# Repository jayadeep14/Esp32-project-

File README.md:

# Esp32 Project
## [ESP32 Bluetooth speaker ](https://github.com/jayadeep14/Esp32-project-/tree/Bt_speaker).
###      Custom ESP32 Bluetooth speaker
         Creating a custom bluetooth speaker using esp32.Esp32 for bluetooth connectivity , a DAC (Digital-to-Analog  
         Converter) for audio quality, potentially an amplifier, and a battery with a charging circuit.

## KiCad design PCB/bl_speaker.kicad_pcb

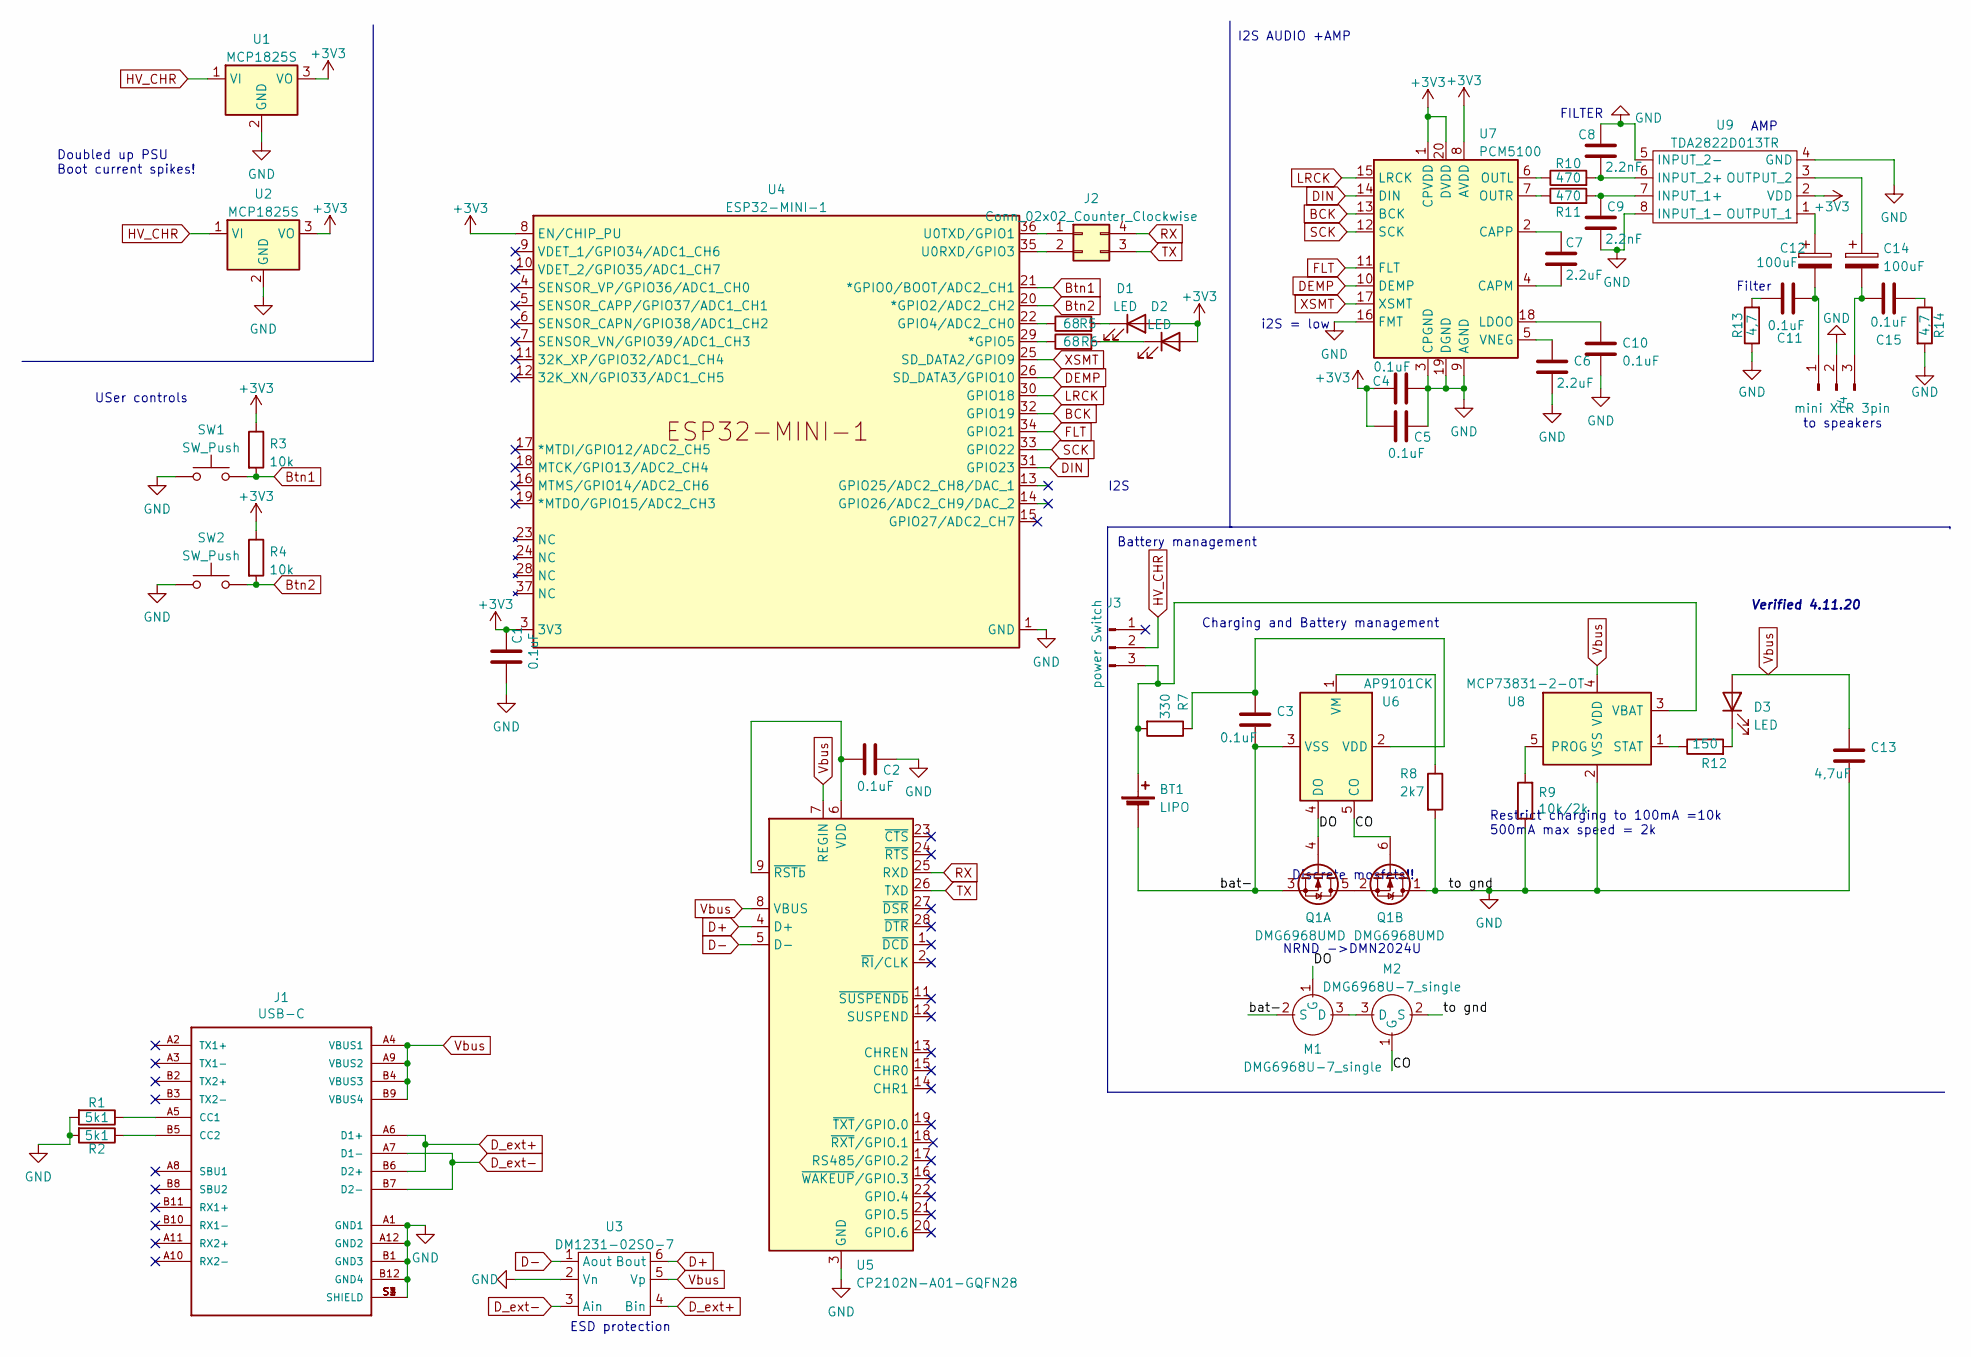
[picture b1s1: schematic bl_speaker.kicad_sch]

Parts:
BT1: LIPO; PinHeader_1x02_P2.54mm_Vertical
C1, C2, C3, C4, C5, C10, C11, C15: 0.1uF; C_0603_1608Metric
C6, C7: 2.2uF; C_0805_2012Metric
C8, C9: 2.2nF; C_0603_1608Metric
C12, C14: 100uF; CP_Elec_8x10
C13: 4,7uF; C_0603_1608Metric
D1, D2, D3: LED; LED_0603_1608Metric
J1: USB-C; MOLEX_105450-0101
J2: Conn_02x02_Counter_Clockwise; PinHeader_2x02_P2.54mm_Vertical
J3: power Switch; PinHeader_1x03_P2.54mm_Vertical
J4: mini XLR 3pin; PinHeader_1x03_P2.54mm_Vertical
M1, M2: DMG6968U-7_single; TSOT-23
Q1: DMG6968UMD; SOT-23-6_Handsoldering
R1, R2: 5k1; R_0603_1608Metric
R3, R4: 10k; R_0603_1608Metric
R5, R6: 68; R_0603_1608Metric
R7: 330; R_0603_1608Metric
R8: 2k7; R_0603_1608Metric
R9: 10k/2k; R_0603_1608Metric
R10, R11: 470; R_0603_1608Metric
R12: 150; R_0603_1608Metric
R13, R14: 4,7; R_0603_1608Metric
SW1, SW2: SW_Push; SW_SPST_EVQP0
U1, U2: MCP1825S; SOT-223-3_TabPin2
U3: DM1231-02SO-7; SOT-23-6
U4: ESP32-MINI-1
U5: CP2102N-A01-GQFN28; QFN-28-1EP_5x5mm_P0.5mm_EP3.35x3.35mm
U6: AP9101CK; SOT-23-5
U7: PCM5100; TSSOP-20_4.4x6.5mm_P0.65mm
U8: MCP73831-2-OT; SOT-23-5
U9: TDA2822D013TR; SO-8_3.9x4.9mm_P1.27mm

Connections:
+3V3: C1.2, C4.1, C5.1, D1.2 (A), D2.2 (A), R3.1, R4.1, U1.3 (VO), U2.3 (VO), U4.3 (3V3), U4.8 (EN/CHIP_PU), U7.1 (CPVDD), U7.8 (AVDD), U7.20 (DVDD), U9.2 (VDD)
/CO: M2.1 (G), Q1.6 (G), U6.5 (CO)
/DO: M1.1 (G), Q1.4 (G), U6.4 (DO)
/bat-: BT1.2 (-), C3.2, M1.2 (S), Q1.3 (S), U6.3 (VSS)
BCK: U4.32 (GPIO19), U7.13 (BCK)
Btn1: R3.2, SW1.2, U4.21 (*GPIO0/BOOT/ADC2_CH1)
Btn2: R4.2, SW2.2, U4.20 (*GPIO2/ADC2_CH2)
D+: U3.6 (Bout), U5.4 (D+)
D-: U3.1 (Aout), U5.5 (D-)
DEMP: U4.26 (SD_DATA3/GPIO10), U7.10 (DEMP)
DIN: U4.31 (GPIO23), U7.14 (DIN)
D_ext+: J1.A6 (D1+), J1.B6 (D2+), U3.4 (Bin)
D_ext-: J1.A7 (D1-), J1.B7 (D2-), U3.3 (Ain)
FLT: U4.34 (GPIO21), U7.11 (FLT)
GND: C1.1, C2.2, C4.2, C5.2, C6.2, C8.1, C9.2, C10.2, C13.2, J1.A1 (GND1), J1.A12 (GND2), J1.B1 (GND3), J1.B12 (GND4), J1.S1 (SHIELD), J1.S2 (SHIELD), J1.S3 (SHIELD), J1.S4 (SHIELD), J4.2, M2.2 (S), Q1.1 (D), R1.2, R2.2, R8.2, R9.1, R13.1, R14.2, SW1.1, SW2.1, U1.2 (GND), U2.2 (GND), U3.2 (Vn), U4.1 (GND), U4.2 (GND), U4.27 (GND), U4.38 (GND), U4.39 (GND), U4.40 (GND), U4.41 (GND), U4.42 (GND), U4.43 (GND), U4.44 (GND), U4.45 (GND), U4.46 (GND), U4.47 (GND), U4.48 (GND), U4.49 (GND), U4.50 (GND), U4.51 (GND), U4.52 (GND), U4.53 (GND), U4.54 (GND), U4.55 (GND), U5.3 (GND), U5.29 (GND), U7.3 (CPGND), U7.9 (AGND), U7.16 (FMT), U7.19 (DGND), U8.2 (VSS), U9.4 (GND), U9.5 (INPUT_2-), U9.8 (INPUT_1-)
HV_CHR: J3.2, U1.1 (VI), U2.1 (VI)
LRCK: U4.30 (GPIO18), U7.15 (LRCK)
unnamed: BT1.1 (+), J3.3, R7.2, U8.3 (VBAT)
unnamed: C2.1, U5.6 (VDD), U5.9 (~RSTb)
unnamed: C3.1, R7.1, U6.2 (VDD)
unnamed: C6.1, U7.5 (VNEG)
unnamed: C7.1, U7.2 (CAPP)
unnamed: C7.2, U7.4 (CAPM)
unnamed: C8.2, R10.2, U9.6 (INPUT_2+)
unnamed: C9.1, R11.2, U9.7 (INPUT_1+)
unnamed: C10.1, U7.18 (LDOO)
unnamed: C11.1, C12.2, J4.1
unnamed: C11.2, R13.2
unnamed: C12.1, U9.1 (OUTPUT_1)
unnamed: C14.1, U9.3 (OUTPUT_2)
unnamed: C14.2, C15.1, J4.3
unnamed: C15.2, R14.1
unnamed: D1.1 (K), R5.2
unnamed: D2.1 (K), R6.2
unnamed: D3.1 (K), R12.2
unnamed: J1.A5 (CC1), R1.1
unnamed: J1.B5 (CC2), R2.1
unnamed: J2.1, U4.36 (U0TXD/GPIO1)
unnamed: J2.2, U4.35 (U0RXD/GPIO3)
unnamed: M1.3 (D), M2.3 (D)
unnamed: Q1.2 (S), Q1.5 (D)
unnamed: R5.1, U4.22 (GPIO4/ADC2_CH0)
unnamed: R6.1, U4.29 (*GPIO5)
unnamed: R8.1, U6.1 (VM)
unnamed: R9.2, U8.5 (PROG)
unnamed: R10.1, U7.6 (OUTL)
unnamed: R11.1, U7.7 (OUTR)
unnamed: R12.1, U8.1 (STAT)
RX: J2.4, U5.25 (RXD)
SCK: U4.33 (GPIO22), U7.12 (SCK)
TX: J2.3, U5.26 (TXD)
Vbus: C13.1, D3.2 (A), J1.A4 (VBUS1), J1.A9 (VBUS2), J1.B4 (VBUS3), J1.B9 (VBUS4), U3.5 (Vp), U5.7 (REGIN), U5.8 (VBUS), U8.4 (VDD)
XSMT: U4.25 (SD_DATA2/GPIO9), U7.17 (XSMT)

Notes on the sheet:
I2S
Doubled up PSU Boot current spikes!
ESD protection
Battery management
FILTER
I2S AUDIO +AMP
Charging and Battery management
NRND ->DMN2024U
AMP
Verified 4.11.20
Filter
i2S = low
Restrict charging to 100mA =10k 500mA max speed = 2k
Discrete mosfets!!
to speakers
USer controls

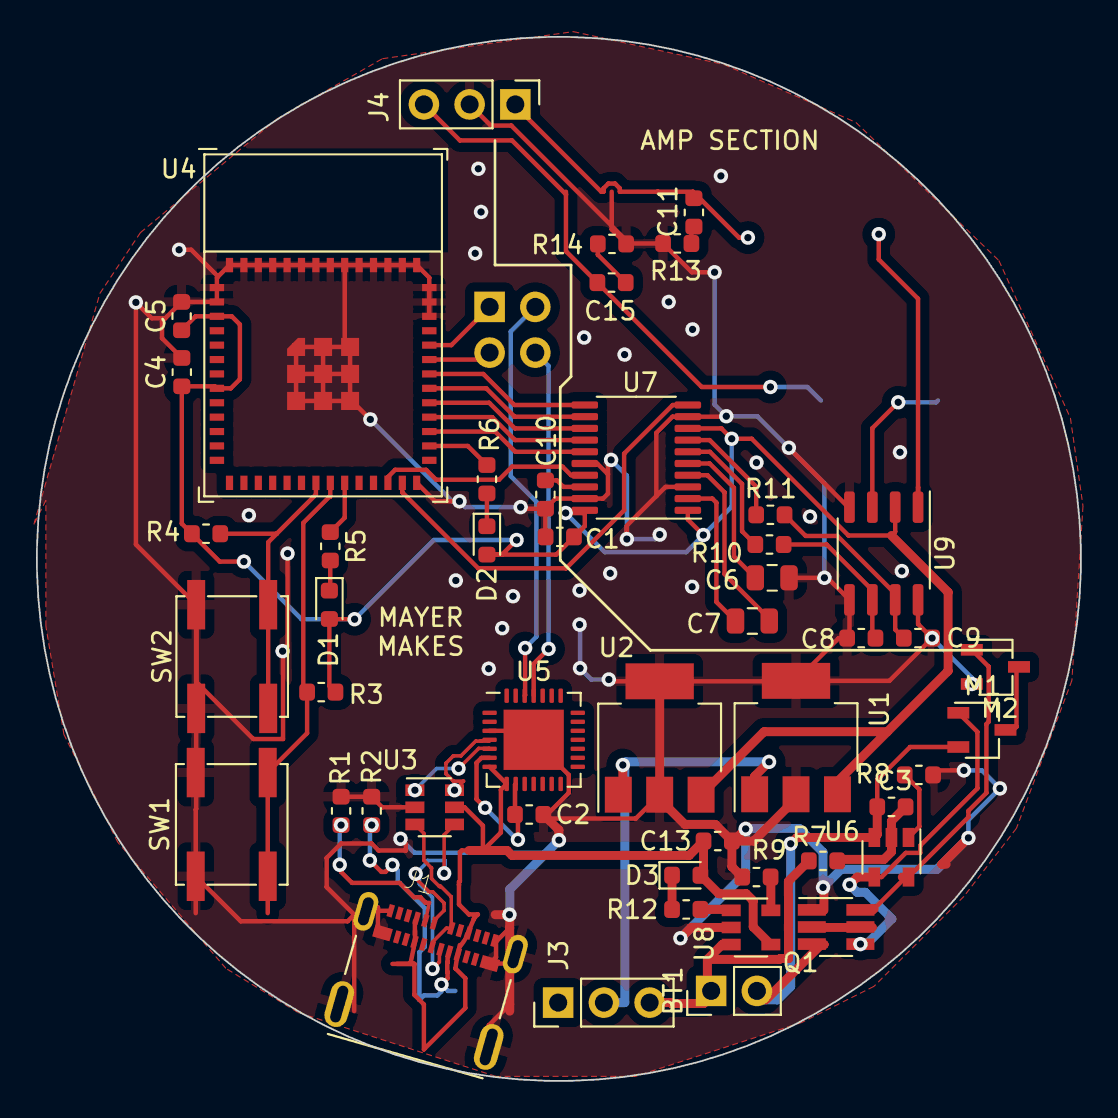
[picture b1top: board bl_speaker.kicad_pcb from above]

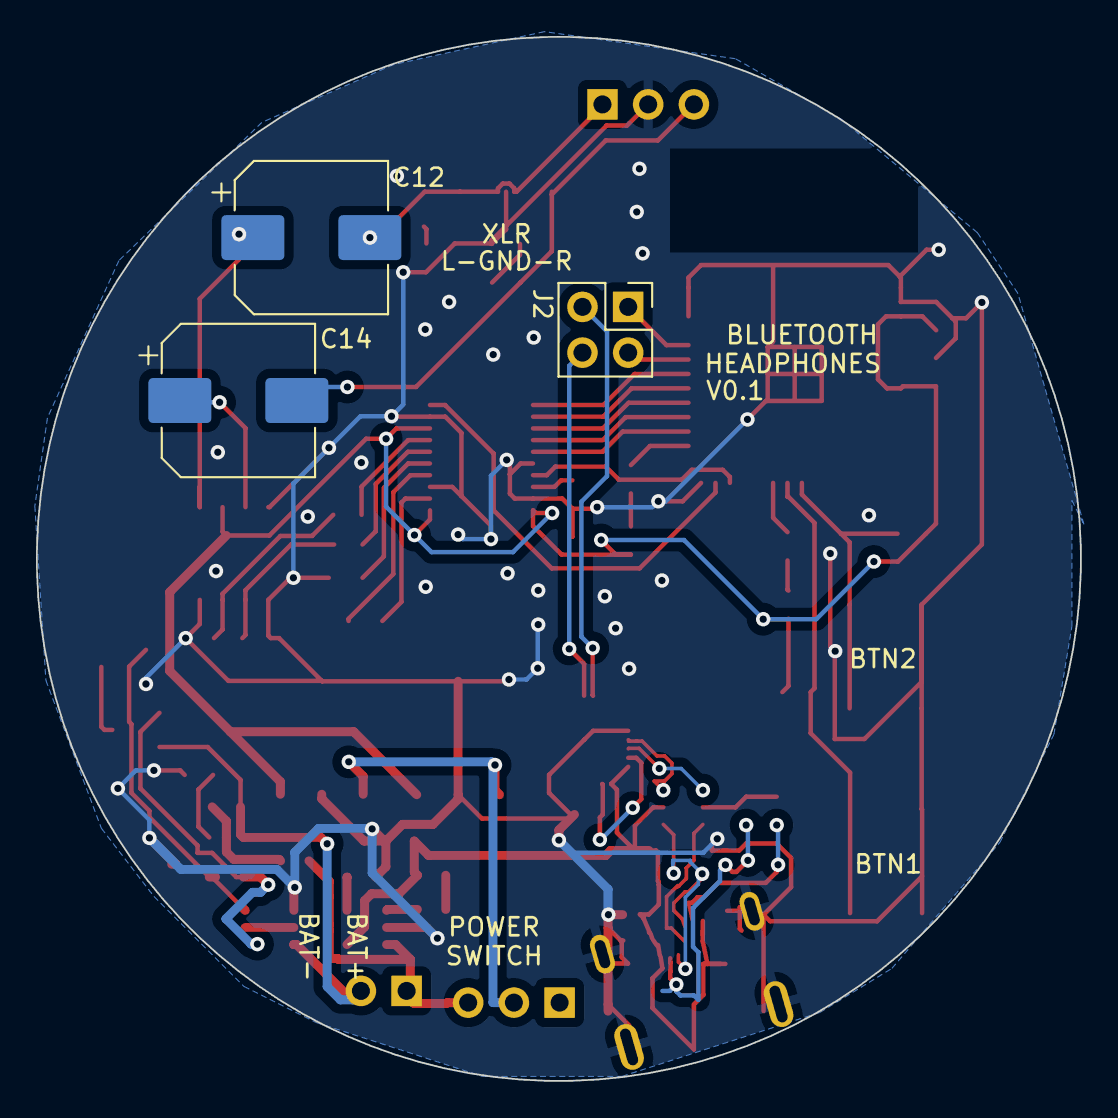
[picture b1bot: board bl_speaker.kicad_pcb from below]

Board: 2 copper layers, 58.0 x 58.0 mm, 51 parts (3 on the bottom side), 53 nets.

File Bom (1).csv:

Comment,Val,Package,Mid X,Mid Y,Rotation,Layer
C12,100uF,CP_Elec_8x10,-166.25,-78.400384,180,bottom
C14,100uF,CP_Elec_8x10,-170.305985,-87.450384,180,bottom
C1,0.1uF,C_0603_1608Metric,152.55,-95.025,0,top
C2,0.1uF,C_0603_1608Metric,150.848485,-110.450384,0,top
C3,0.1uF,C_0603_1608Metric,170.973485,-110.025384,180,top
C4,0.1uF,C_0603_1608Metric,131.55,-85.875,90,top
C5,0.1uF,C_0603_1608Metric,131.539999,-82.760002,90,top
C6,2.2uF,C_0805_2012Metric,164.348485,-97.300384,0,top
C7,2.2uF,C_0805_2012Metric,163.248485,-99.700384,0,top
C8,2.2nF,C_0603_1608Metric,169.298487,-100.65038,0,top
C9,2.2nF,C_0603_1608Metric,172.448485,-100.650384,0,top
C10,0.1uF,C_0603_1608Metric,151.75,-92.675,-90,top
C11,0.1uF,C_0603_1608Metric,160,-77,-90,top
C13,"4,7uF",C_0603_1608Metric,161.323483,-111.925381,0,top
C15,0.1uF,C_0603_1608Metric,155.425,-80.9,0,top
D1,LED,LED_0603_1608Metric,139.748485,-98.800384,-90,top
D2,LED,LED_0603_1608Metric,148.5,-95.225,-90,top
D3,LED,LED_0603_1608Metric,159.573485,-113.825383,0,top
M1,DMG6968U-7_single,TSOT-23,176,-105.75,0,top
M2,DMG6968U-7_single,TSOT-23,176.75,-102.25,0,top
Q1,DMG6968UMD,SOT-23-6_Handsoldering,167.9,-116.7,0,top
R1,5k1,R_0603_1608Metric,140.398482,-110.25,90,top
R2,5k1,R_0603_1608Metric,142.098481,-110.25,90,top
R3,10k,R_0603_1608Metric,139.298485,-103.650384,180,top
R4,10k,R_0603_1608Metric,132.898485,-94.850384,0,top
R5,68,R_0603_1608Metric,139.798485,-95.550384,-90,top
R6,68,R_0603_1608Metric,148.5,-91.824997,-90,top
R7,330,R_0603_1608Metric,167.173484,-113.025383,180,top
R8,2k7,R_0603_1608Metric,172.5,-108.25,0,top
R9,10k/2k,R_0603_1608Metric,163.473483,-113.925383,0,top
R10,470,R_0603_1608Metric,164.198485,-95.450384,0,top
R11,470,R_0603_1608Metric,164.248485,-93.800384,0,top
R12,150,R_0603_1608Metric,159.573485,-115.725384,180,top
R13,"4,7",R_0603_1608Metric,159.073485,-78.725384,0,top
R14,"4,7",R_0603_1608Metric,155.448485,-78.750384,0,top
SW1,SW_Push,SW_SPST_EVQP0,134.323485,-111,90,top
SW2,SW_Push,SW_SPST_EVQP0,134.348485,-101.675384,90,top
U1,MCP1825S,SOT-223-3_TabPin2,165.673485,-106.175384,90,top
U2,MCP1825S,SOT-223-3_TabPin2,158.098485,-106.200384,90,top
U3,DM1231-02SO-7,SOT-23-6,145.6,-110.05,0,top
U4,ESP32-MINI-1,ESP32-MINI-1,139.4,-85.975,0,top
U5,CP2102N-A01-GQFN28,QFN-28-1EP_5x5mm_P0.5mm_EP3.35x3.35mm,151.098485,-106.300384,0,top
U6,AP9101CK,SOT-23-5,170.973483,-112.825383,-90,top
U7,PCM5100,TSSOP-20_4.4x6.5mm_P0.65mm,156.8,-90.625,180,top
U8,MCP73831-2-OT,SOT-23-5,163.173485,-116.725384,0,top
U9,TDA2822D013TR,SO-8_3.9x4.9mm_P1.27mm,170.548485,-95.950384,-90,top

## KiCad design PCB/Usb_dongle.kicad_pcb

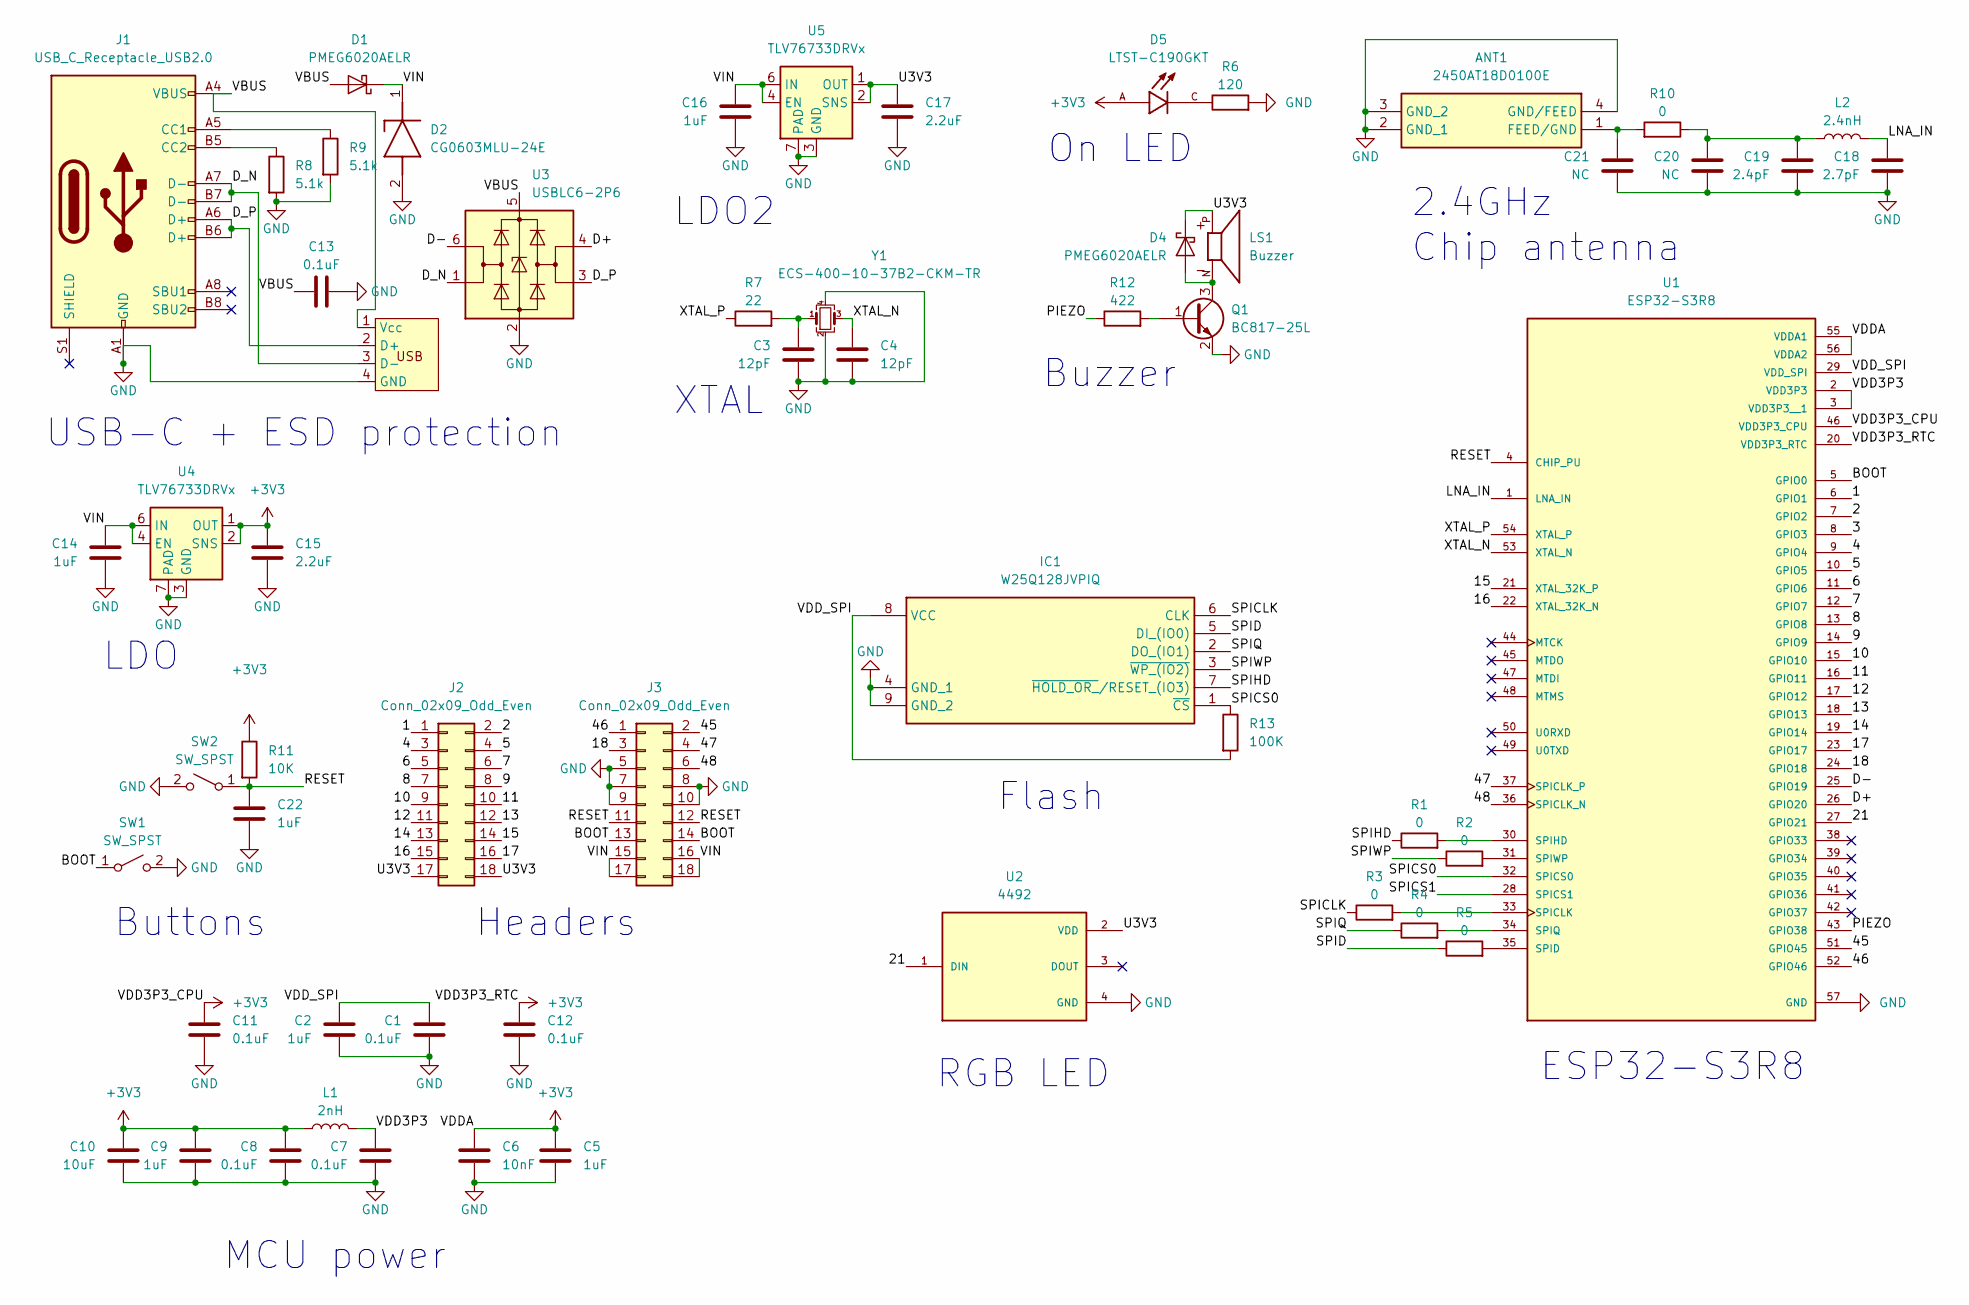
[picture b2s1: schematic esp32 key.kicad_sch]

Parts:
ANT1: 2450AT18D0100E; Manufacturer_Part_Number 2450AT18D0100E; Mouser Part Number 609-2450AT18D0100E
C1, C7, C8, C11, C12, C13: 0.1uF; R_0402_1005Metric
C2, C5, C9, C22: 1uF; R_0402_1005Metric
C3, C4: 12pF; R_0201_0603Metric
C6: 10nF; R_0201_0603Metric
C10: 10uF; R_0603_1608Metric
C14, C16: 1uF; R_0603_1608Metric
C15, C17: 2.2uF; R_0402_1005Metric
C18: 2.7pF; R_0201_0603Metric
C19: 2.4pF; R_0201_0603Metric
C20, C21: NC; R_0201_0603Metric
D1, D4: PMEG6020AELR; Nexperia_CFP3_SOD-123W
D2: CG0603MLU-24E; Manufacturer_Part_Number CG0603MLU-24E; Mouser Part Number 652-CG0603MLU-24E
D5: LTST-C190GKT; LEDC1608X35N
IC1: W25Q128JVPIQ; Manufacturer_Part_Number W25Q128JVPIQ; Mouser Part Number 454-W25Q128JVPIQ
J1: USB_C_Receptacle_USB2.0; USB_C_Receptacle_GCT_USB4105-xx-A_16P_TopMnt_Horizontal
J2, J3: Conn_02x09_Odd_Even; PinHeader_2x09_P2.54mm_Vertical
L1: 2nH; L_0402_1005Metric
L2: 2.4nH; L_0201_0603Metric
LS1: Buzzer; XDCR_CMT-0525-75-SMT-TR; PARTREV 1.0
Q1: BC817-25L; SOT-23
R1, R2, R3, R4, R5, R10: 0; R_0201_0603Metric
R6: 120; R_0402_1005Metric
R7: 22; R_0402_1005Metric
R8, R9: 5.1k; R_0402_1005Metric
R11: 10K; R_0402_1005Metric
R12: 422; R_0402_1005Metric
R13: 100K; R_0201_0603Metric
SW1, SW2: SW_SPST; SW_SPST_PTS810
U1: ESP32-S3R8; QFN40P700X700X90-57N-D
U2: 4492; SK6805-EC15; PARTREV 14/10/19
U3: USBLC6-2P6; SOT-666
U4, U5: TLV76733DRVx; WSON-6-1EP_2x2mm_P0.65mm_EP1x1.6mm_ThermalVias
U6: PCB_usb
Y1: ECS-400-10-37B2-CKM-TR; Crystal_SMD_2016-4Pin_2.0x1.6mm

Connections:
+3V3: C5.1, C6.1, C8.1, C9.1, C10.1, C11.1, C12.1, C15.1, D5.A, L1.2, R11.1, U1.20 (VDD3P3_RTC), U1.46 (VDD3P3_CPU), U1.55 (VDDA1), U1.56 (VDDA2), U4.1 (OUT), U4.2 (SNS)
/1: J2.1, U1.6 (GPIO1)
/2: J2.2, U1.7 (GPIO2)
/3: U1.8 (GPIO3)
/4: J2.3, U1.9 (GPIO4)
/5: J2.4, U1.10 (GPIO5)
/6: J2.5, U1.11 (GPIO6)
/7: J2.6, U1.12 (GPIO7)
/8: J2.7, U1.13 (GPIO8)
/9: J2.8, U1.14 (GPIO9)
/10: J2.9, U1.15 (GPIO10)
/11: J2.10, U1.16 (GPIO11)
/12: J2.11, U1.17 (GPIO12)
/13: J2.12, U1.18 (GPIO13)
/14: J2.13, U1.19 (GPIO14)
/15: J2.14, U1.21 (XTAL_32K_P)
/16: J2.15, U1.22 (XTAL_32K_N)
/17: J2.16, U1.23 (GPIO17)
/18: J3.3, U1.24 (GPIO18)
/21: U1.27 (GPIO21), U2.1 (DIN)
/45: J3.2, U1.51 (GPIO45)
/46: J3.1, U1.52 (GPIO46)
/47: J3.4, U1.37 (SPICLK_P)
/48: J3.6, U1.36 (SPICLK_N)
/BOOT: J3.13, J3.14, SW1.1 (A), U1.5 (GPIO0)
/D+: U1.26 (GPIO20), U3.4 (I/O2)
/D-: U1.25 (GPIO19), U3.6 (I/O1)
/D_N: J1.A7 (D-), J1.B7 (D-), U3.1 (I/O1), U6.3 (D-)
/D_P: J1.A6 (D+), J1.B6 (D+), U3.3 (I/O2), U6.2 (D+)
/LNA_IN: C18.1, L2.1, U1.1 (LNA_IN)
/PIEZO: R12.1, U1.43 (GPIO38)
/RESET: C22.1, J3.11, J3.12, R11.2, SW2.1 (A), U1.4 (CHIP_PU)
/SPICLK: IC1.6 (CLK), R3.1
/SPICS0: IC1.1 (~CS), R13.1, U1.32 (SPICS0)
/SPICS1: U1.28 (SPICS1)
/SPID: IC1.5 (DI_(IO0)), R5.1
/SPIHD: IC1.7 (~HOLD_OR_/RESET_(IO3)), R1.1
/SPIQ: IC1.2 (DO_(IO1)), R4.1
/SPIWP: IC1.3 (~WP_(IO2)), R2.1
/U3V3: C17.1, D4.1 (K), J2.17, J2.18, LS1.P, U2.2 (VDD), U5.1 (OUT), U5.2 (SNS)
/VBUS: C13.1, D1.2 (A), J1.A4 (VBUS), J1.A9 (VBUS), J1.B4 (VBUS), J1.B9 (VBUS), U3.5 (VBUS), U6.1 (Vcc)
/VDD3P3: C7.1, L1.1, U1.2 (VDD3P3), U1.3 (VDD3P3__1)
/VDD_SPI: C1.1, C2.1, IC1.8 (VCC), R13.2, U1.29 (VDD_SPI)
/VIN: C14.1, C16.1, D1.1 (K), D2.1 (K), J3.15, J3.16, J3.17, J3.18, U4.4 (EN), U4.6 (IN), U5.4 (EN), U5.6 (IN)
/XTAL_N: C4.1, U1.53 (XTAL_N), Y1.3
/XTAL_P: R7.1, U1.54 (XTAL_P)
GND: ANT1.2 (GND_1), ANT1.3 (GND_2), ANT1.4 (GND/FEED), C1.2, C2.2, C3.2, C4.2, C5.2, C6.2, C7.2, C8.2, C9.2, C10.2, C11.2, C12.2, C13.2, C14.2, C15.2, C16.2, C17.2, C18.2, C19.2, C20.2, C21.2, C22.2, D2.2 (A), IC1.4 (GND_1), IC1.9 (GND_2), J1.A1 (GND), J1.A12 (GND), J1.B1 (GND), J1.B12 (GND), J3.5, J3.7, J3.8, J3.9, J3.10, Q1.2 (E), R6.2, R8.2, R9.2, SW1.2 (B), SW2.2 (B), U1.57 (GND), U2.4 (GND), U3.2 (GND), U4.3 (GND), U4.5 (GND), U4.7 (PAD), U5.3 (GND), U5.5 (GND), U5.7 (PAD), U6.4 (GND), Y1.2, Y1.4
unnamed: ANT1.1 (FEED/GND), C21.1, R10.2
unnamed: C3.1, R7.2, Y1.1
unnamed: C19.1, C20.1, L2.2, R10.1
unnamed: D4.2 (A), LS1.N, Q1.3 (C)
unnamed: D5.C, R6.1
unnamed: J1.A5 (CC1), R9.1
unnamed: J1.B5 (CC2), R8.1
unnamed: Q1.1 (B), R12.2
unnamed: R3.2, U1.33 (SPICLK)
unnamed: R5.2, U1.35 (SPID)
unnamed: R1.2, U1.30 (SPIHD)
unnamed: R4.2, U1.34 (SPIQ)
unnamed: R2.2, U1.31 (SPIWP)

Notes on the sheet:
LDO
Buzzer
Buttons
RGB LED
Flash
USB-C + ESD protection
Chip antenna
Headers
XTAL
MCU power
On LED
2.4GHz
ESP32-S3R8
LDO2

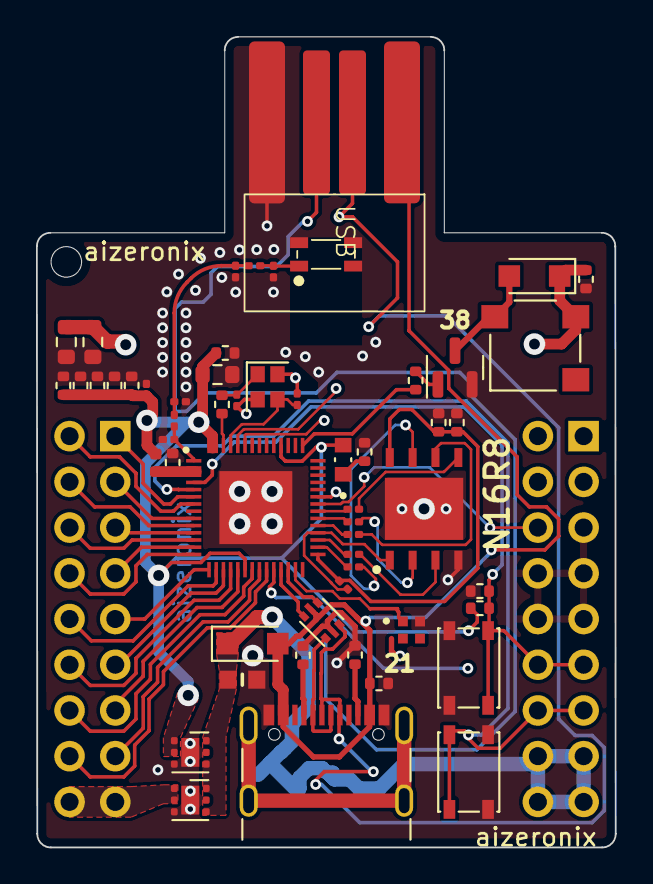
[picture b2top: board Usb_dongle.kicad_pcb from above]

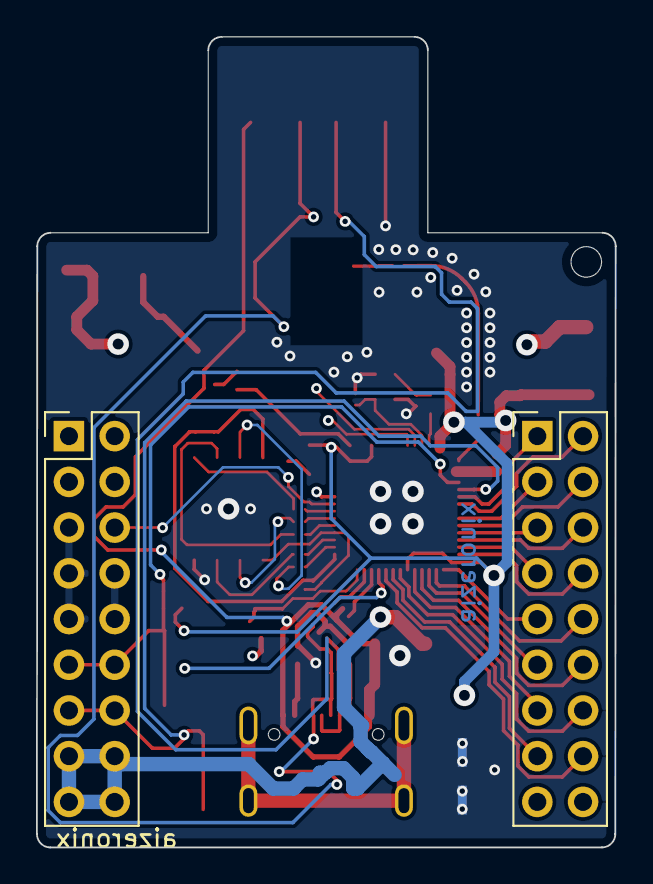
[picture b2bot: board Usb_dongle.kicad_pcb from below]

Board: 4 copper layers, 32.2 x 45.0 mm, 57 parts (2 on the bottom side), 58 nets.

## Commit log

2025-11-25 Add initial README for Esp32 project
2025-11-25 Rename Read.md to README.md
2025-11-25 Add initial README for Bt_speaker project
2025-11-25 Rename Bt_speaker/gerber (1).zip to Bt_speaker/PCB/gerber (1).zip
2025-11-25 Add contribution guidelines link to README
2025-11-25 Update contribution guidelines link in README
2025-11-25 Add link to Bluetooth speaker case file in README
    Added a link to the Bluetooth speaker case file.
2025-11-26 Fix file name casing for README.md
2025-11-26 Fix link path for Bluetooth speaker section
2025-11-26 Enhance README with images and project details
    Added images and improved description for the ESP32 Bluetooth speaker project.
2025-11-26 Remove redundant project title from README
2025-11-26 Rename README.md to Readme.md
2025-11-26 Enhance Readme with images and project details
    Added an image and improved project description.
2025-11-26 Rename PCB/bl_speaker.pdf to Layers.pdf
2025-11-26 Remove empty line from README.md
2025-11-26 Create PCB
2025-11-26 Create e
2025-11-26 Rename PCB/esp32 key.pdf to Schematic.pdf
2025-11-26 Rename PCB/esp32 key.png to esp32 key.png
2025-11-26 Rename esp32 key.png to Photo.png
2025-11-26 Rename esp32 key.kicad_pcb to Usb_dongle.kicad_pcb
2025-11-26 Add esp32 key PCB file
